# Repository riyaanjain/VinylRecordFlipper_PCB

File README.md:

# 🎵 Automatic Vinyl Record Flipper

I love vinyl records.

But each side of a 12 inch LP can only store about 20 minutes of music, and I don't necessarily love having to get up to flip the record often. I just wish that, after I put the record on, it would play the entire album.

So, we took matters into our own hands and built an **automatic vinyl record flipper**.

Included are:
- **PCB Design Files**
- **The program code**
- **A picture and video for your enjoyment (have to download the video from Image_and_Video folder🥲)**
- **Design Document**

Hopefully you enjoy it as much as I did!

---

## 🧠 What It Does

This device automatically flips a vinyl record by sending PWM signals to servo motors using an ESP32 microcontroller. It detects the tonearm rest position using a Hall effect sensor, then triggers the motors to lift, rotate, and drop the record back down.

---

## 🖼️ Project Gallery

### 🔧 PCB Preview  

### 📸 Final Project Photo

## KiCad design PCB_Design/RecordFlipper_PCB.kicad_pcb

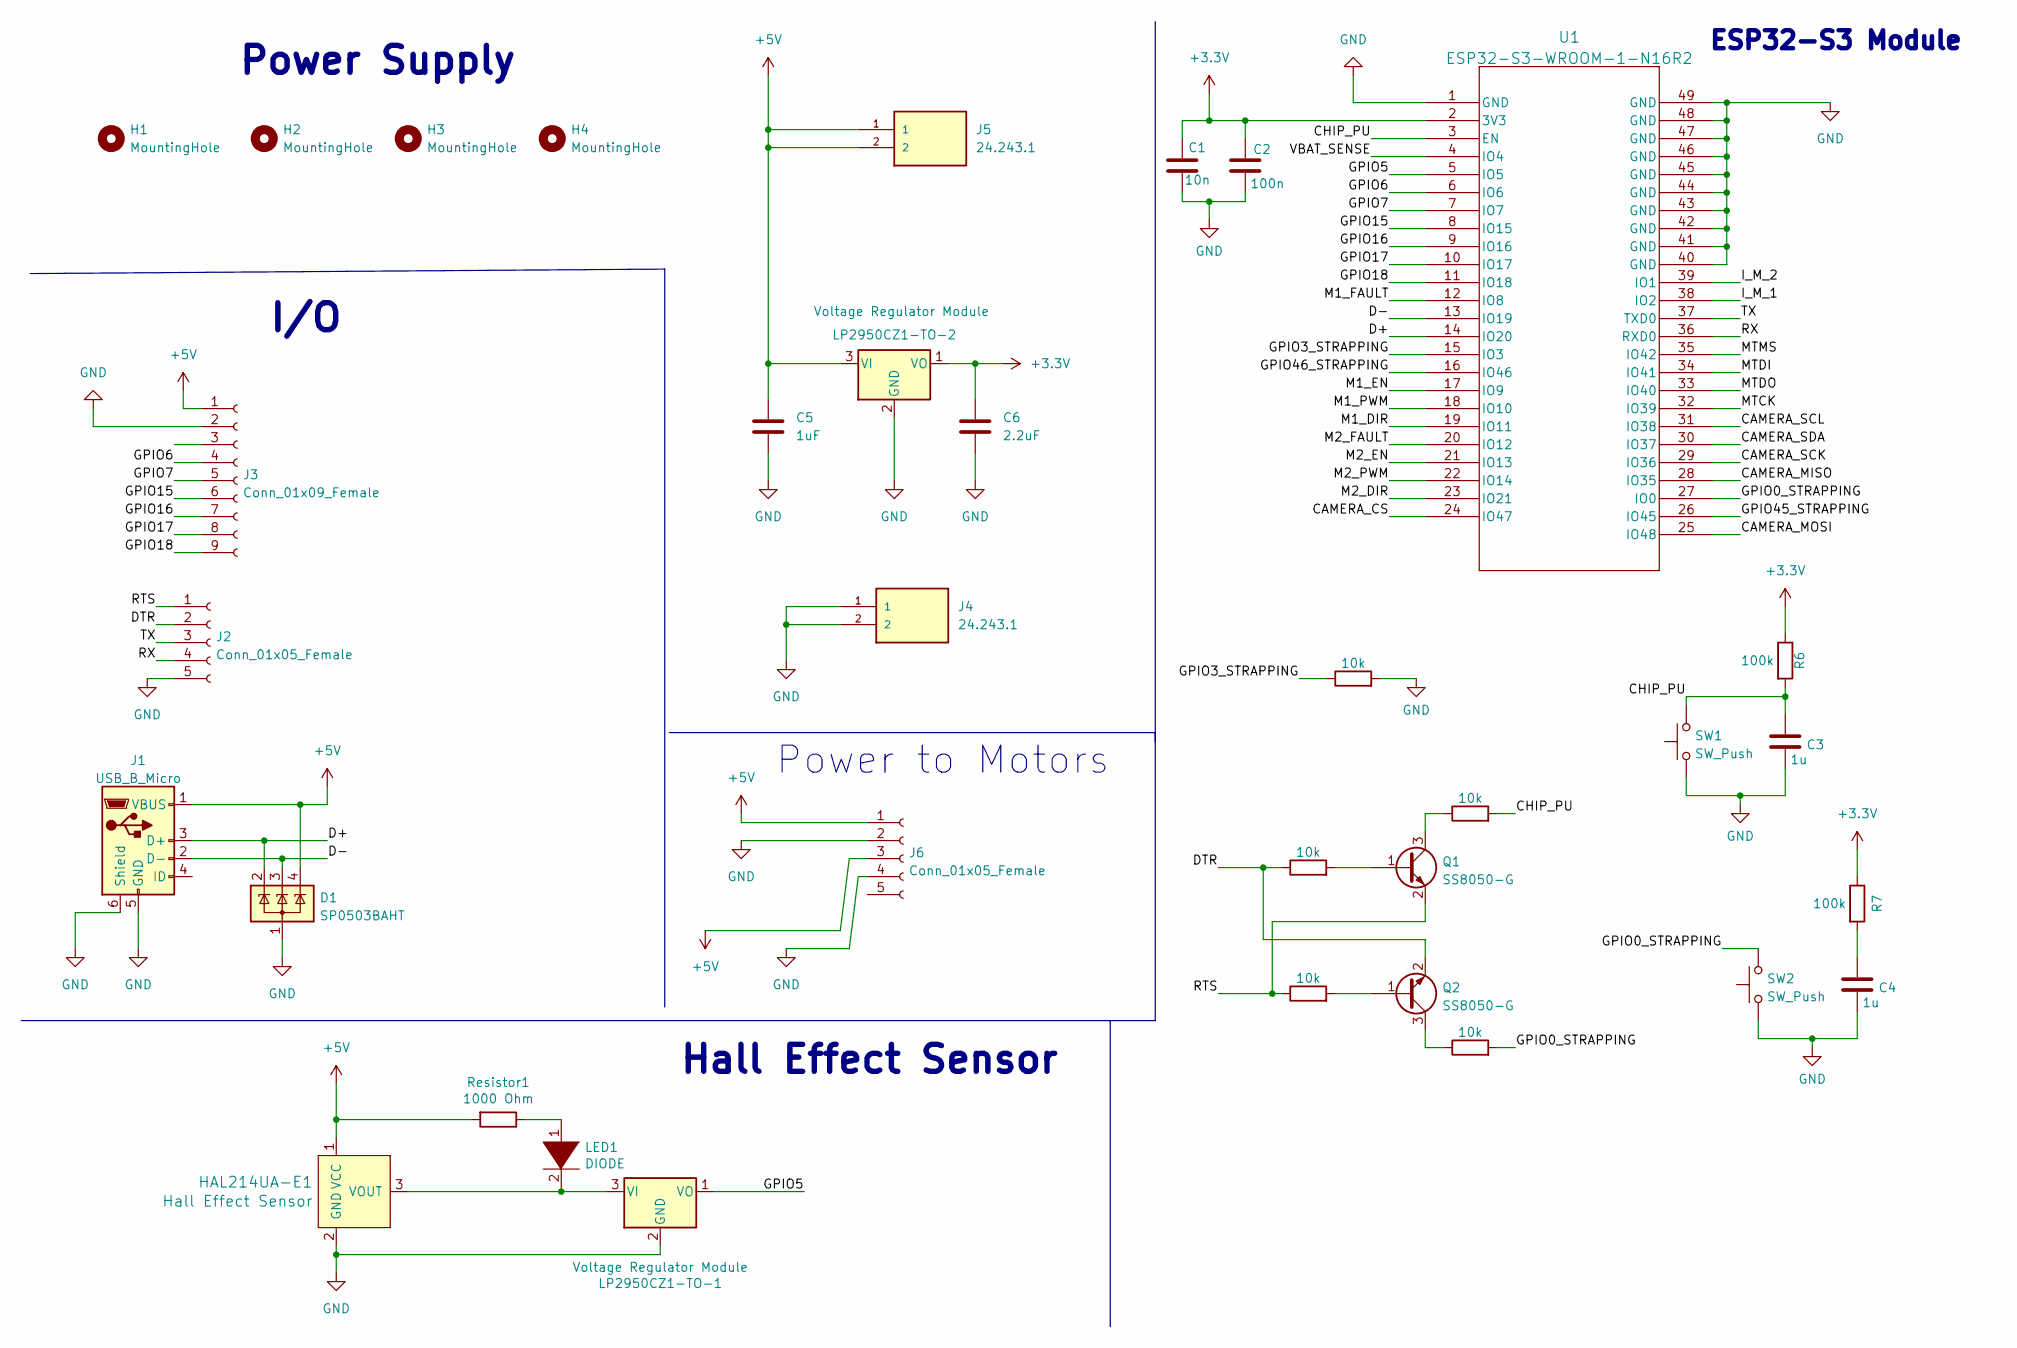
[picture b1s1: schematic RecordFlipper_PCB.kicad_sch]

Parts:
C1: 10n; C_0805_2012Metric
C2: 100n; C_0805_2012Metric
C3, C4: 1u; C_0805_2012Metric
C5: 1uF; C_0805_2012Metric_Pad1.18x1.45mm_HandSolder
C6: 2.2uF; C_0805_2012Metric_Pad1.18x1.45mm_HandSolder
D1: SP0503BAHT; SOT-143
H1, H2, H3, H4: MountingHole; MountingHole_3.2mm_M3
HAL214UA-E1: Hall Effect Sensor; TO92127P460H470-3; MPN A1326LUA-T; Digi-Key_PN 620-1433-ND
J1: USB_B_Micro; USB_Micro-B_Amphenol_10118194_Horizontal
J2, J6: Conn_01x05_Female; PinHeader_1x05_P2.54mm_Vertical
J3: Conn_01x09_Female; PinHeader_1x09_P2.54mm_Vertical
J4, J5: 24.243.1; 242431; Manufacturer_Part_Number 24.243.1
LED1: DIODE; LED_5mm_Radial
LP2950CZ1-TO-1, LP2950CZ1-TO-2: Voltage Regulator Module; TO-92-3
Q1, Q2: SS8050-G; SOT-23
R1, R2, R3, R4, R5: 10k; R_0805_2012Metric
R6, R7: 100k; R_0805_2012Metric
Resistor1: 1000 Ohm; R_0805_2012Metric
SW1, SW2: SW_Push; SW_SPST_B3S-1000
U1: ESP32-S3-WROOM-1-N16R2; ESP32-S3-WROOM-1_EXP

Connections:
+3.3V: C1.1, C2.1, C6.1, LP2950CZ1-TO-2.1 (VO), R6.1, R7.1, U1.2 (3V3)
+5V: C5.1, D1.4 (K), HAL214UA-E1.1 (VCC), J1.1 (VBUS), J3.1, J5.1, J5.2, J6.1, J6.3, LP2950CZ1-TO-2.3 (VI), Resistor1.2
/CAMERA_CS: U1.24 (IO47)
/CAMERA_MISO: U1.28 (IO35)
/CAMERA_MOSI: U1.25 (IO48)
/CAMERA_SCK: U1.29 (IO36)
/CAMERA_SCL: U1.31 (IO38)
/CAMERA_SDA: U1.30 (IO37)
/CHIP_PU: C3.1, R4.2, R6.2, SW1.2, U1.3 (EN)
/D+: D1.2 (K), J1.3 (D+), U1.14 (IO20)
/D-: D1.3 (K), J1.2 (D-), U1.13 (IO19)
/DTR: J2.2, Q2.2 (E), R1.1
/GPIO0_STRAPPING: R5.2, SW2.2, U1.27 (IO0)
/GPIO3_STRAPPING: R3.1, U1.15 (IO3)
/GPIO5: LP2950CZ1-TO-1.1 (VO), U1.5 (IO5)
/GPIO6: J3.4, U1.6 (IO6)
/GPIO7: J3.5, U1.7 (IO7)
/GPIO15: J3.6, U1.8 (IO15)
/GPIO16: J3.7, U1.9 (IO16)
/GPIO17: J3.8, U1.10 (IO17)
/GPIO18: J3.9, U1.11 (IO18)
/GPIO45_STRAPPING: U1.26 (IO45)
/GPIO46_STRAPPING: U1.16 (IO46)
/I_M_1: U1.38 (IO2)
/I_M_2: U1.39 (IO1)
/M1_DIR: U1.19 (IO11)
/M1_EN: U1.17 (IO9)
/M1_FAULT: U1.12 (IO8)
/M1_PWM: U1.18 (IO10)
/M2_DIR: U1.23 (IO21)
/M2_EN: U1.21 (IO13)
/M2_FAULT: U1.20 (IO12)
/M2_PWM: U1.22 (IO14)
/MTCK: U1.32 (IO39)
/MTDI: U1.34 (IO41)
/MTDO: U1.33 (IO40)
/MTMS: U1.35 (IO42)
/RTS: J2.1, Q1.2 (E), R2.1
/RX: J2.4, U1.36 (RXD0)
/TX: J2.3, U1.37 (TXD0)
/VBAT_SENSE: U1.4 (IO4)
GND: C1.2, C2.2, C3.2, C4.2, C5.2, C6.2, D1.1 (A), HAL214UA-E1.2 (GND), J1.5 (GND), J1.6 (Shield), J2.5, J3.2, J4.1, J4.2, J6.2, J6.4, LP2950CZ1-TO-1.2 (GND), LP2950CZ1-TO-2.2 (GND), R3.2, SW1.1, SW2.1, U1.1 (GND), U1.40 (GND), U1.41 (GND), U1.42 (GND), U1.43 (GND), U1.44 (GND), U1.45 (GND), U1.46 (GND), U1.47 (GND), U1.48 (GND), U1.49 (GND)
unnamed: C4.1, R7.2
unnamed: HAL214UA-E1.3 (VOUT), LED1.2 (A), LP2950CZ1-TO-1.3 (VI)
unnamed: LED1.1 (K), Resistor1.1
unnamed: Q1.1 (B), R1.2
unnamed: Q1.3 (C), R4.1
unnamed: Q2.1 (B), R2.2
unnamed: Q2.3 (C), R5.1

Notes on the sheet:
Hall Effect Sensor
ESP32-S3 Module
Power to Motors
Power Supply
I/O

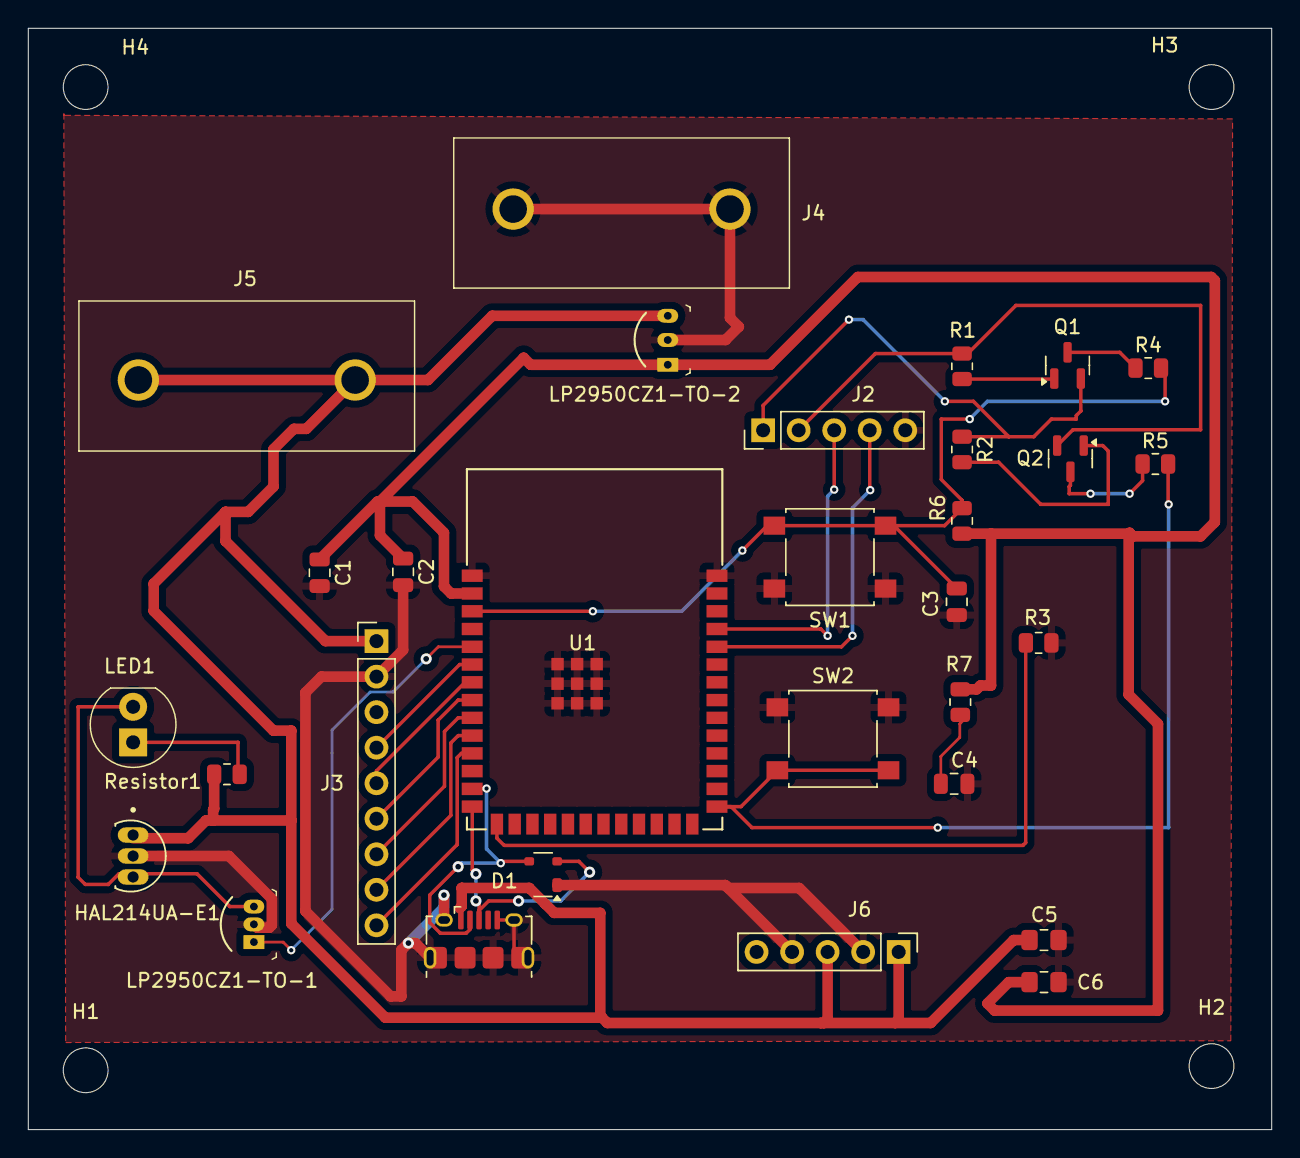
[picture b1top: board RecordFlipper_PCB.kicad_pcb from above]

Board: 2 copper layers, 88.9 x 78.7 mm, 34 parts (0 on the bottom side), 26 nets.

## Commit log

2025-04-29 Initial commit: Automatic Vinyl Record Flipper project
2025-04-30 Deleted image files from Image_and_Video
2025-04-30 Removed project_photo.jpeg and project_video.mp4 from Image_and_Video
2025-12-03 Uploaded design document
2025-12-03 Rename Record_Flipper_Program.ino to Program Code.ino
